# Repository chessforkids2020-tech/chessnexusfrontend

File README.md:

# chess-competition

## Getting started

To make it easy for you to get started with GitLab, here's a list of recommended next steps.

Already a pro? Just edit this README.md and make it your own. Want to make it easy? [Use the template at the bottom](#editing-this-readme)!

## Add your files

* [Create](https://docs.gitlab.com/ee/user/project/repository/web_editor.html#create-a-file) or [upload](https://docs.gitlab.com/ee/user/project/repository/web_editor.html#upload-a-file) files
* [Add files using the command line](https://docs.gitlab.com/topics/git/add_files/#add-files-to-a-git-repository) or push an existing Git repository with the following command:

```
cd existing_repo
git remote add origin https://gitlab.com/chess9832746/chess-competition.git
git branch -M main
git push -uf origin main
```

## Integrate with your tools

* [Set up project integrations](https://gitlab.com/chess9832746/chess-competition/-/settings/integrations)

## Collaborate with your team

* [Invite team members and collaborators](https://docs.gitlab.com/ee/user/project/members/)
* [Create a new merge request](https://docs.gitlab.com/ee/user/project/merge_requests/creating_merge_requests.html)
* [Automatically close issues from merge requests](https://docs.gitlab.com/ee/user/project/issues/managing_issues.html#closing-issues-automatically)
* [Enable merge request approvals](https://docs.gitlab.com/ee/user/project/merge_requests/approvals/)
* [Set auto-merge](https://docs.gitlab.com/user/project/merge_requests/auto_merge/)

## Test and Deploy

Use the built-in continuous integration in GitLab.

* [Get started with GitLab CI/CD](https://docs.gitlab.com/ee/ci/quick_start/)
* [Analyze your code for known vulnerabilities with Static Application Security Testing (SAST)](https://docs.gitlab.com/ee/user/application_security/sast/)
* [Deploy to Kubernetes, Amazon EC2, or Amazon ECS using Auto Deploy](https://docs.gitlab.com/ee/topics/autodevops/requirements.html)
* [Use pull-based deployments for improved Kubernetes management](https://docs.gitlab.com/ee/user/clusters/agent/)
* [Set up protected environments](https://docs.gitlab.com/ee/ci/environments/protected_environments.html)

***

# Editing this README

When you're ready to make this README your own, just edit this file and use the handy template below (or feel free to structure it however you want - this is just a starting point!). Thanks to [makeareadme.com](https://www.makeareadme.com/) for this template.

## Suggestions for a good README

Every project is different, so consider which of these sections apply to yours. The sections used in the template are suggestions for most open source projects. Also keep in mind that while a README can be too long and detailed, too long is better than too short. If you think your README is too long, consider utilizing another form of documentation rather than cutting out information.

## Name
Choose a self-explaining name for your project.

## Description
Let people know what your project can do specifically. Provide context and add a link to any reference visitors might be unfamiliar with. A list of Features or a Background subsection can also be added here. If there are alternatives to your project, this is a good place to list differentiating factors.

## Badges
On some READMEs, you may see small images that convey metadata, such as whether or not all the tests are passing for the project. You can use Shields to add some to your README. Many services also have instructions for adding a badge.

## Visuals
Depending on what you are making, it can be a good idea to include screenshots or even a video (you'll frequently see GIFs rather than actual videos). Tools like ttygif can help, but check out Asciinema for a more sophisticated method.

## Installation
Within a particular ecosystem, there may be a common way of installing things, such as using Yarn, NuGet, or Homebrew. However, consider the possibility that whoever is reading your README is a novice and would like more guidance. Listing specific steps helps remove ambiguity and gets people to using your project as quickly as possible. If it only runs in a specific context like a particular programming language version or operating system or has dependencies that have to be installed manually, also add a Requirements subsection.

## Usage
Use examples liberally, and show the expected output if you can. It's helpful to have inline the smallest example of usage that you can demonstrate, while providing links to more sophisticated examples if they are too long to reasonably include in the README.

## Support
Tell people where they can go to for help. It can be any combination of an issue tracker, a chat room, an email address, etc.

## Roadmap
If you have ideas for releases in the future, it is a good idea to list them in the README.

## Contributing
State if you are open to contributions and what your requirements are for accepting them.

For people who want to make changes to your project, it's helpful to have some documentation on how to get started. Perhaps there is a script that they should run or some environment variables that they need to set. Make these steps explicit. These instructions could also be useful to your future self.

You can also document commands to lint the code or run tests. These steps help to ensure high code quality and reduce the likelihood that the changes inadvertently break something. Having instructions for running tests is especially helpful if it requires external setup, such as starting a Selenium server for testing in a browser.

## Authors and acknowledgment
Show your appreciation to those who have contributed to the project.

## License
For open source projects, say how it is licensed.

## Project status
If you have run out of energy or time for your project, put a note at the top of the README saying that development has slowed down or stopped completely. Someone may choose to fork your project or volunteer to step in as a maintainer or owner, allowing your project to keep going. You can also make an explicit request for maintainers.

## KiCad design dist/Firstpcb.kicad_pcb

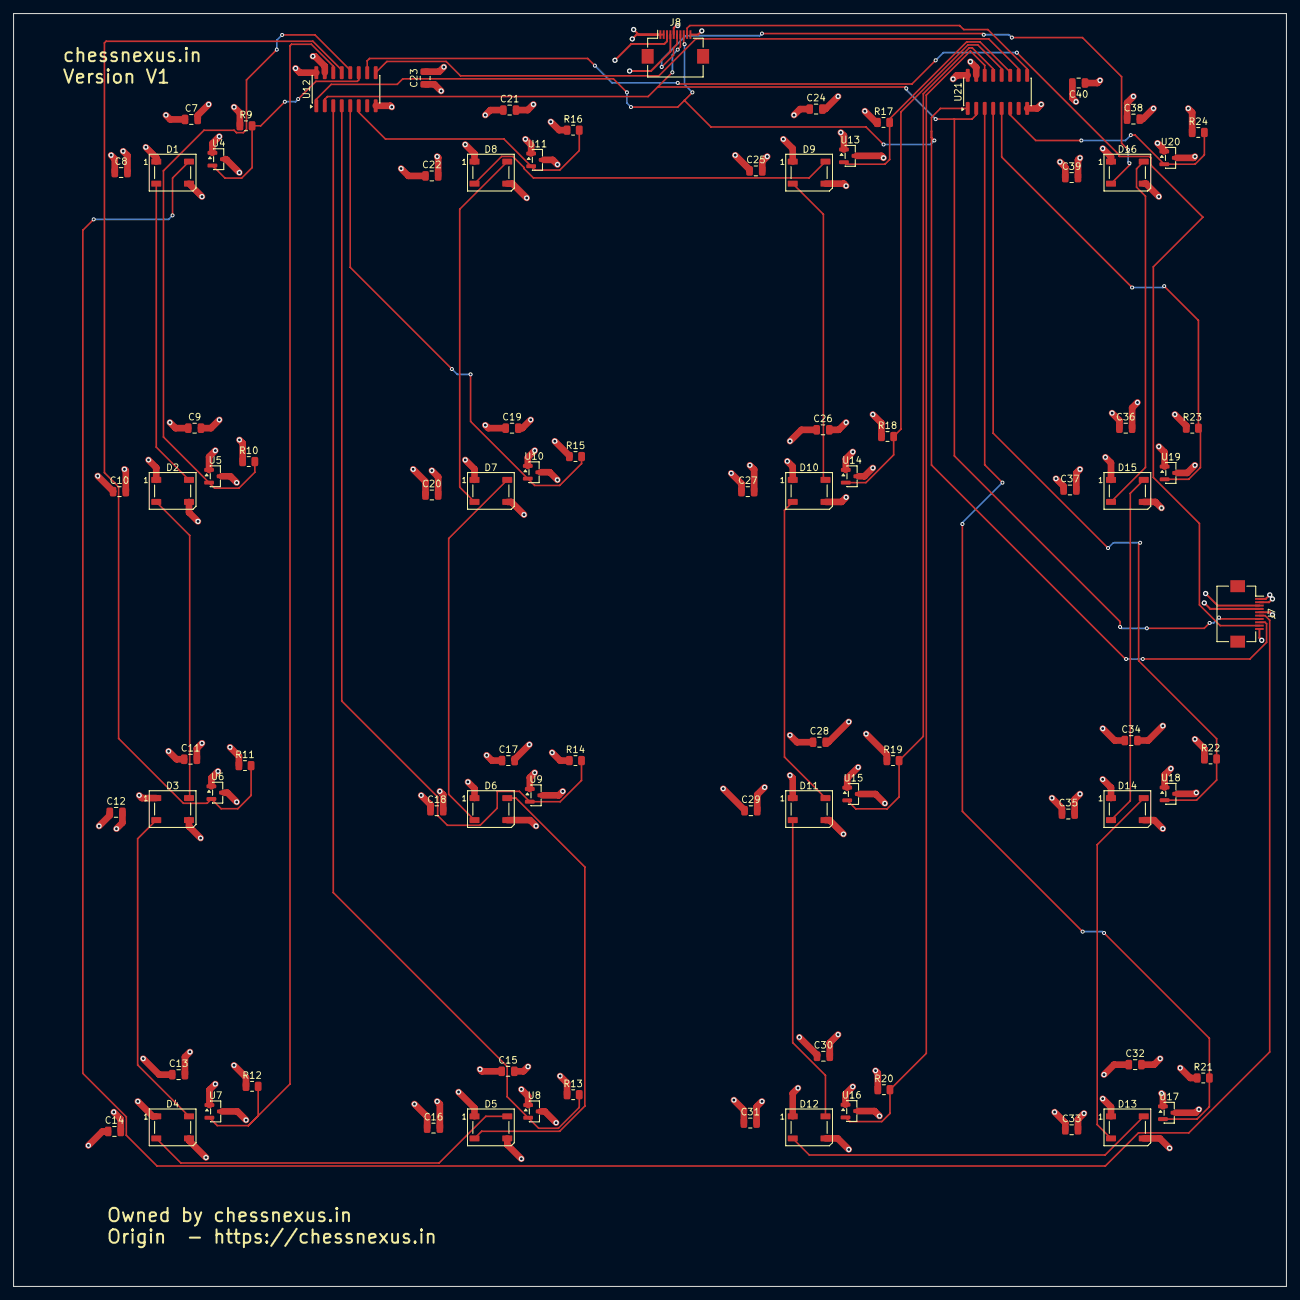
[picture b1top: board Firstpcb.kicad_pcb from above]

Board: 4 copper layers, 190.5 x 190.5 mm, 86 parts (0 on the bottom side), 41 nets.

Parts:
C7, C8, C9, C10, C11, C12, C13, C14, C15, C16, C17, C18, C19, C20, C21, C22, C23, C24, C25, C26, C27, C28, C29, C30, C31, C32, C33, C34, C35, C36, C37, C38, C39, C40: 100nF; C_0805_2012Metric
D1, D2, D3, D4, D5, D6, D7, D8, D9, D10, D11, D12, D13, D14, D15, D16: WS2812B-B/T; LED_WS2812B_PLCC4_5.0x5.0mm_P3.2mm
J7, J8: Conn_01x10; Hirose_FH12-10S-0.5SH_1x10-1MP_P0.50mm_Horizontal
R9, R10, R11, R12, R13, R14, R15, R16, R17, R18, R19, R20, R21, R22, R23, R24: 10k; R_0805_2012Metric
U4, U5, U6, U7, U8, U9, U10, U11, U13, U14, U15, U16, U17, U18, U19, U20: DRV5033FAQDBZR; SOT-23
U12, U21: 74HC165; SOIC-16_3.9x9.9mm_P1.27mm

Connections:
+3V3: C7.1, C9.1, C11.1, C13.1, C15.1, C17.1, C19.1, C21.1, C23.1, C24.1, C26.1, C28.1, C30.1, C32.1, C34.1, C36.1, C38.1, C40.1, J7.5, J8.5, R9.1, R10.1, R11.1, R12.1, R13.1, R14.1, R15.1, R16.1, R17.1, R18.1, R19.1, R20.1, R21.1, R22.1, R23.1, R24.1, U4.1 (VCC), U5.1 (VCC), U6.1 (VCC), U7.1 (VCC), U8.1 (VCC), U9.1 (VCC), U10.1 (VCC), U11.1 (VCC), U12.16 (VCC), U13.1 (VCC), U14.1 (VCC), U15.1 (VCC), U16.1 (VCC), U17.1 (VCC), U18.1 (VCC), U19.1 (VCC), U20.1 (VCC), U21.16 (VCC)
+5V: C8.1, C10.1, C12.1, C14.1, C16.1, C18.1, C20.1, C22.1, C25.1, C27.1, C29.1, C31.1, C33.1, C35.1, C37.1, C39.1, D1.1 (VDD), D2.1 (VDD), D3.1 (VDD), D4.1 (VDD), D5.1 (VDD), D6.1 (VDD), D7.1 (VDD), D8.1 (VDD), D9.1 (VDD), D10.1 (VDD), D11.1 (VDD), D12.1 (VDD), D13.1 (VDD), D14.1 (VDD), D15.1 (VDD), D16.1 (VDD), J7.1, J7.2, J8.1, J8.2
/LED_DATA_5V: D1.4 (DIN), J7.6
/LED_DOUT: D16.2 (DOUT), J8.6
/SENSE_CLK: J7.7, J8.7, U12.2 (CP), U21.2 (CP)
/SENSE_IN: J7.9, U12.10 (DS)
/SENSE_LOAD: J7.8, J8.8, U12.1 (~PL), U21.1 (~PL)
/SENSE_OUT: J8.9, U21.9 (Q7)
/row1/LED_OUT: D8.2 (DOUT), D9.4 (DIN)
/row1/SENSE_OUT: U12.9 (Q7), U21.10 (DS)
/row1/SQ_a1: R9.2, U4.2 (OUT), U12.11 (D0)
/row1/SQ_b1: R10.2, U5.2 (OUT), U12.12 (D1)
/row1/SQ_c1: R11.2, U6.2 (OUT), U12.13 (D2)
/row1/SQ_d1: R12.2, U7.2 (OUT), U12.14 (D3)
/row1/SQ_e1: R13.2, U8.2 (OUT), U12.3 (D4)
/row1/SQ_f1: R14.2, U9.2 (OUT), U12.4 (D5)
/row1/SQ_g1: R15.2, U10.2 (OUT), U12.5 (D6)
/row1/SQ_h1: R16.2, U11.2 (OUT), U12.6 (D7)
/row2/SQ_a1: R17.2, U13.2 (OUT), U21.11 (D0)
/row2/SQ_b1: R18.2, U14.2 (OUT), U21.12 (D1)
/row2/SQ_c1: R19.2, U15.2 (OUT), U21.13 (D2)
/row2/SQ_d1: R20.2, U16.2 (OUT), U21.14 (D3)
/row2/SQ_e1: R21.2, U17.2 (OUT), U21.3 (D4)
/row2/SQ_f1: R22.2, U18.2 (OUT), U21.4 (D5)
/row2/SQ_g1: R23.2, U19.2 (OUT), U21.5 (D6)
/row2/SQ_h1: R24.2, U20.2 (OUT), U21.6 (D7)
GND: C7.2, C8.2, C9.2, C10.2, C11.2, C12.2, C13.2, C14.2, C15.2, C16.2, C17.2, C18.2, C19.2, C20.2, C21.2, C22.2, C23.2, C24.2, C25.2, C26.2, C27.2, C28.2, C29.2, C30.2, C31.2, C32.2, C33.2, C34.2, C35.2, C36.2, C37.2, C38.2, C39.2, C40.2, D1.3 (VSS), D2.3 (VSS), D3.3 (VSS), D4.3 (VSS), D5.3 (VSS), D6.3 (VSS), D7.3 (VSS), D8.3 (VSS), D9.3 (VSS), D10.3 (VSS), D11.3 (VSS), D12.3 (VSS), D13.3 (VSS), D14.3 (VSS), D15.3 (VSS), D16.3 (VSS), J7.3, J7.4, J7.10, J8.3, J8.4, J8.10, U4.3 (GND), U5.3 (GND), U6.3 (GND), U7.3 (GND), U8.3 (GND), U9.3 (GND), U10.3 (GND), U11.3 (GND), U12.8 (GND), U12.15 (~CE), U13.3 (GND), U14.3 (GND), U15.3 (GND), U16.3 (GND), U17.3 (GND), U18.3 (GND), U19.3 (GND), U20.3 (GND), U21.8 (GND), U21.15 (~CE)
unnamed: D1.2 (DOUT), D2.4 (DIN)
unnamed: D2.2 (DOUT), D3.4 (DIN)
unnamed: D3.2 (DOUT), D4.4 (DIN)
unnamed: D4.2 (DOUT), D5.4 (DIN)
unnamed: D5.2 (DOUT), D6.4 (DIN)
unnamed: D6.2 (DOUT), D7.4 (DIN)
unnamed: D7.2 (DOUT), D8.4 (DIN)
unnamed: D9.2 (DOUT), D10.4 (DIN)
unnamed: D10.2 (DOUT), D11.4 (DIN)
unnamed: D11.2 (DOUT), D12.4 (DIN)
unnamed: D12.2 (DOUT), D13.4 (DIN)
unnamed: D13.2 (DOUT), D14.4 (DIN)
unnamed: D14.2 (DOUT), D15.4 (DIN)
unnamed: D15.2 (DOUT), D16.4 (DIN)
